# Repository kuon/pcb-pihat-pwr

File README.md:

## Simple power hat for the raspberry pi

This power hat provides 3A power to the raspberry pi from a 5-15V input with an
additional 5V 2A output.

Library footprint and symbols are from <https://github.com/goyman/pcb-kicad-lib>

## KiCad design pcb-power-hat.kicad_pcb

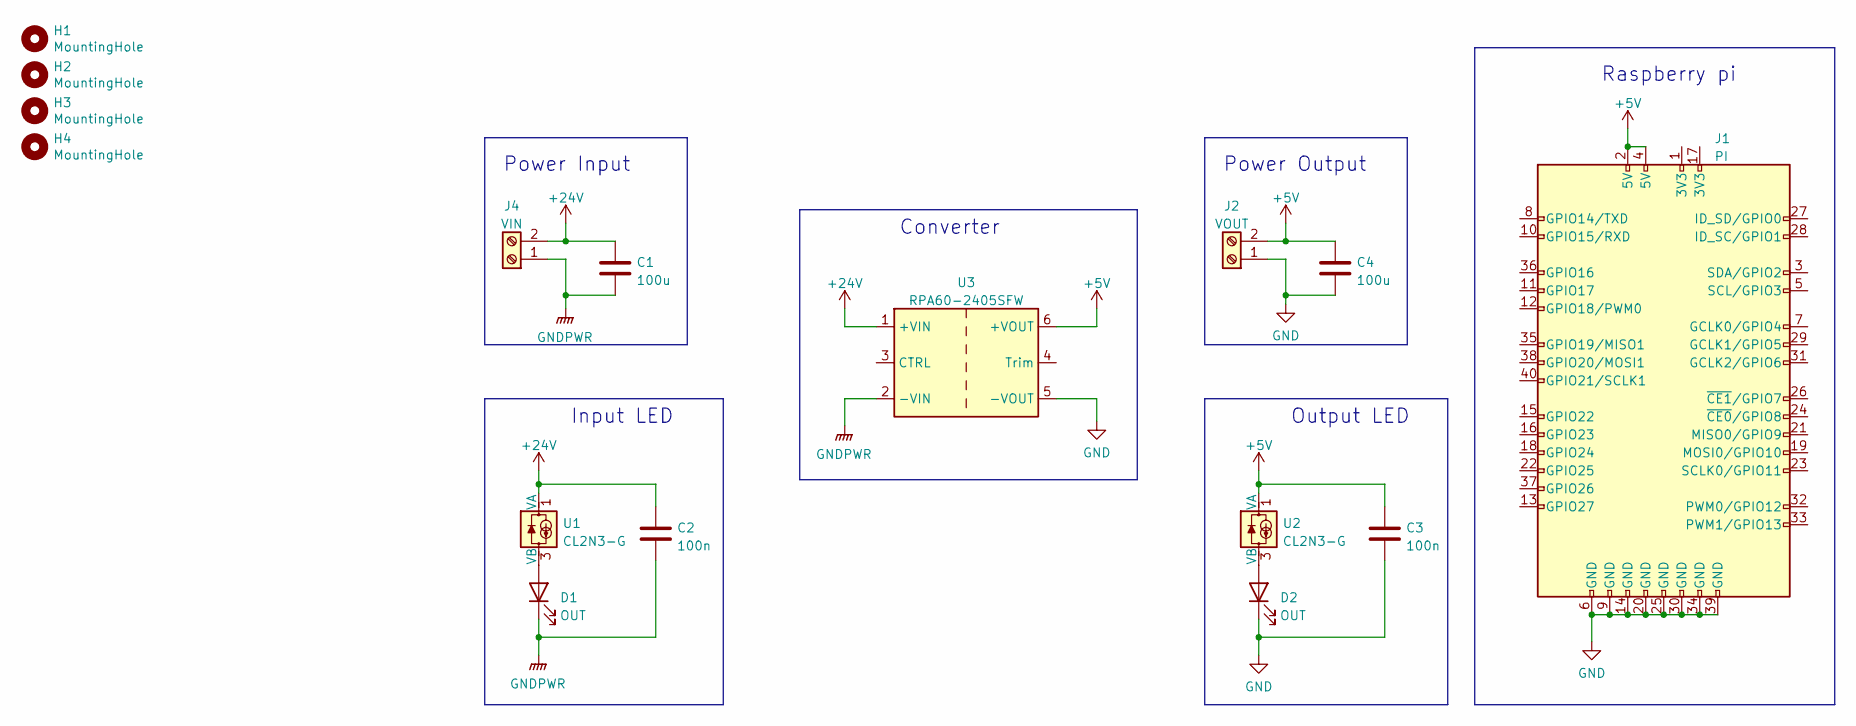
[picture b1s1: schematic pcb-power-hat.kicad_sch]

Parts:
C1, C4: 100u; CP_Radial_Tantal_D10.5mm_P5.00mm
C2, C3: 100n; C_Rect_L7.0mm_W3.5mm_P5.00mm; MPN C322C104K5R5TA
D1, D2: OUT; LED_D3.0mm
H1, H2, H3, H4: MountingHole; MountingHole_3.2mm_M3
J1: PI; PinSocket_2x20_P2.54mm_Vertical; MPN SSQ-120-03-T-D
J2: VOUT; TerminalBlock_bornier-2_P5.08mm; MPN 691103110002
J4: VIN; TerminalBlock_bornier-2_P5.08mm; MPN 691103110002
U1, U2: CL2N3-G; TO-92L_Inline_Wide
U3: RPA60-2405SFW; Converter_DCDC_RECOM_RPA60-xxxxSFW

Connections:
+5V: C3.1, C4.1, J1.2 (5V), J1.4 (5V), J2.2, U2.1 (VA), U3.6 (+VOUT)
+24V: C1.1, C2.1, J4.2, U1.1 (VA), U3.1 (+VIN)
GND: C3.2, C4.2, D2.1 (K), J1.6 (GND), J1.9 (GND), J1.14 (GND), J1.20 (GND), J1.25 (GND), J1.30 (GND), J1.34 (GND), J1.39 (GND), J2.1, U3.5 (-VOUT)
GNDPWR: C1.2, C2.2, D1.1 (K), J4.1, U3.2 (-VIN)
unnamed: D1.2 (A), U1.3 (VB)
unnamed: D2.2 (A), U2.3 (VB)

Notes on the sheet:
Input LED
Raspberry pi
Output LED
Converter
Power Output
Power Input

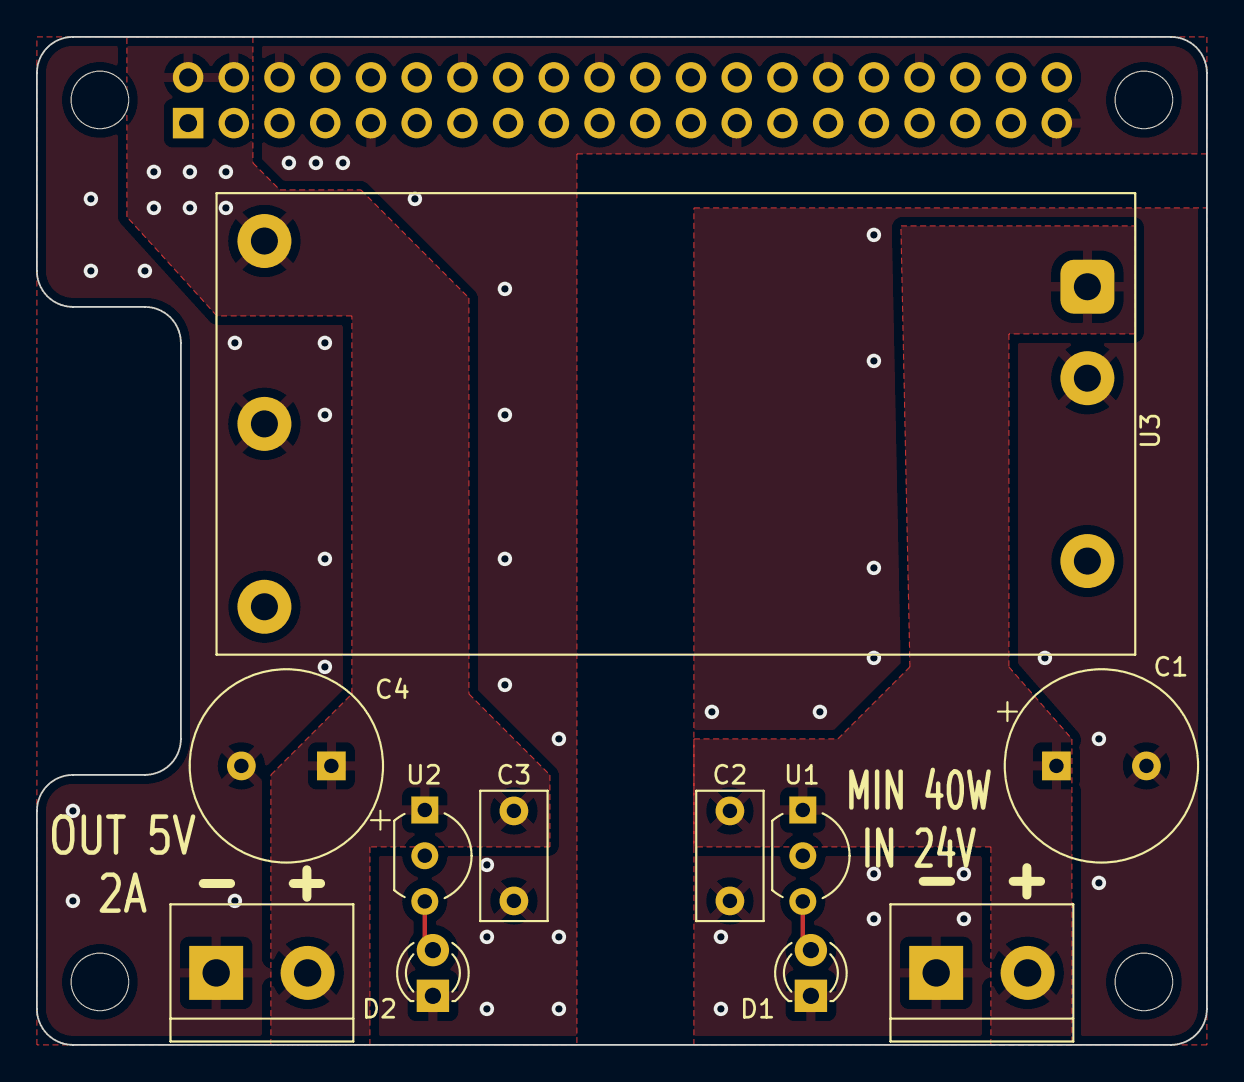
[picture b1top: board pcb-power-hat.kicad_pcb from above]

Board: 2 copper layers, 65.0 x 56.0 mm, 16 parts (1 on the bottom side), 6 nets.

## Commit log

2022-05-29 Rev 1
2022-05-29 Add readme
2022-05-29 Add board image
2022-06-02 Reduce resistor for violet LED as it has 3.3V voltage drop.
2022-06-09 Fix TVS footprint
2022-10-22 Add IPN
2022-10-22 Move to standard module based solution
